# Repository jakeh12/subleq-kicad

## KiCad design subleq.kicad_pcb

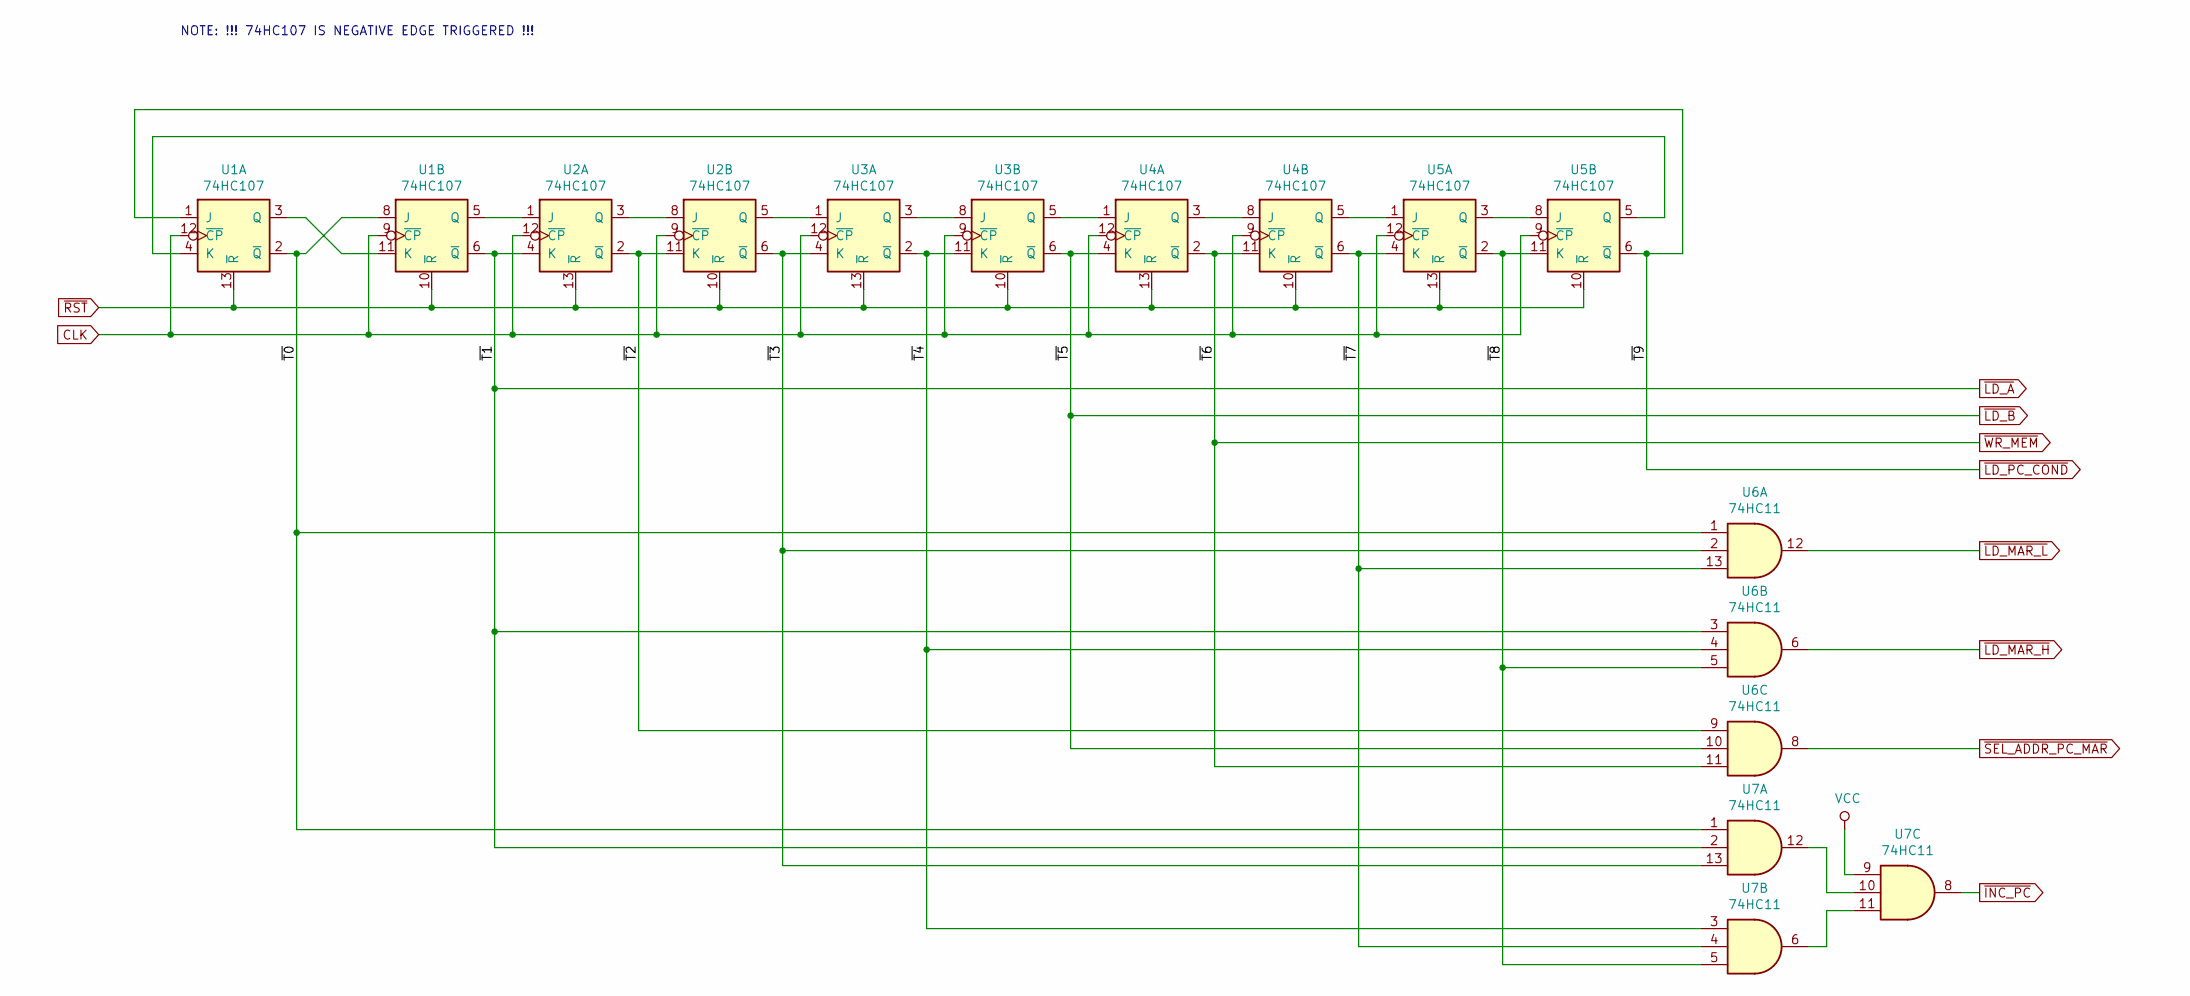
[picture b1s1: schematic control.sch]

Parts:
U1, U2, U3, U4, U5: 74HC107; DIP-14_W7.62mm
U6, U7: 74HC11; DIP-14_W7.62mm

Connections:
/CONTROL/~T0: U1.2 (~Q), U1.8 (J), U6.1, U7.1
/CONTROL/~T2: U2.2 (~Q), U2.11 (K), U6.9
/CONTROL/~T3: U2.6 (~Q), U3.4 (K), U6.2, U7.13
/CONTROL/~T4: U3.2 (~Q), U3.11 (K), U6.4, U7.3
/CONTROL/~T7: U4.6 (~Q), U5.4 (K), U6.13, U7.4
/CONTROL/~T8: U5.2 (~Q), U5.11 (K), U6.5, U7.5
CLK: U1.9 (~CP), U1.12 (~CP), U2.9 (~CP), U2.12 (~CP), U3.9 (~CP), U3.12 (~CP), U4.9 (~CP), U4.12 (~CP), U5.9 (~CP), U5.12 (~CP); also elsewhere on the board
unnamed: U1.4 (K), U5.5 (Q)
unnamed: U1.5 (Q), U2.1 (J)
unnamed: U1.3 (Q), U1.11 (K)
unnamed: U2.3 (Q), U2.8 (J)
unnamed: U2.5 (Q), U3.1 (J)
unnamed: U3.3 (Q), U3.8 (J)
unnamed: U3.5 (Q), U4.1 (J)
unnamed: U4.3 (Q), U4.8 (J)
unnamed: U4.5 (Q), U5.1 (J)
unnamed: U5.3 (Q), U5.8 (J)
unnamed: U7.10, U7.12
unnamed: U7.6, U7.11
VCC: U7.9; also elsewhere on the board
~ADDR_OE: U1.10 (~R), U1.13 (~R), U2.10 (~R), U2.13 (~R), U3.10 (~R), U3.13 (~R), U4.10 (~R), U4.13 (~R), U5.10 (~R), U5.13 (~R); also elsewhere on the board
~INC_PC: U7.8; also elsewhere on the board
~LD_A: U1.6 (~Q), U2.4 (K), U6.3, U7.2; also elsewhere on the board
~LD_B: U3.6 (~Q), U4.4 (K), U6.10; also elsewhere on the board
~LD_MAR_H: U6.6; also elsewhere on the board
~LD_MAR_L: U6.12; also elsewhere on the board
~LD_PC_COND: U1.1 (J), U5.6 (~Q); also elsewhere on the board
~SEL_ADDR_PC_MAR: U6.8; also elsewhere on the board
~WR_MEM: U4.2 (~Q), U4.11 (K), U6.11; also elsewhere on the board

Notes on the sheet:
NOTE: !!! 74HC107 IS NEGATIVE EDGE TRIGGERED !!!

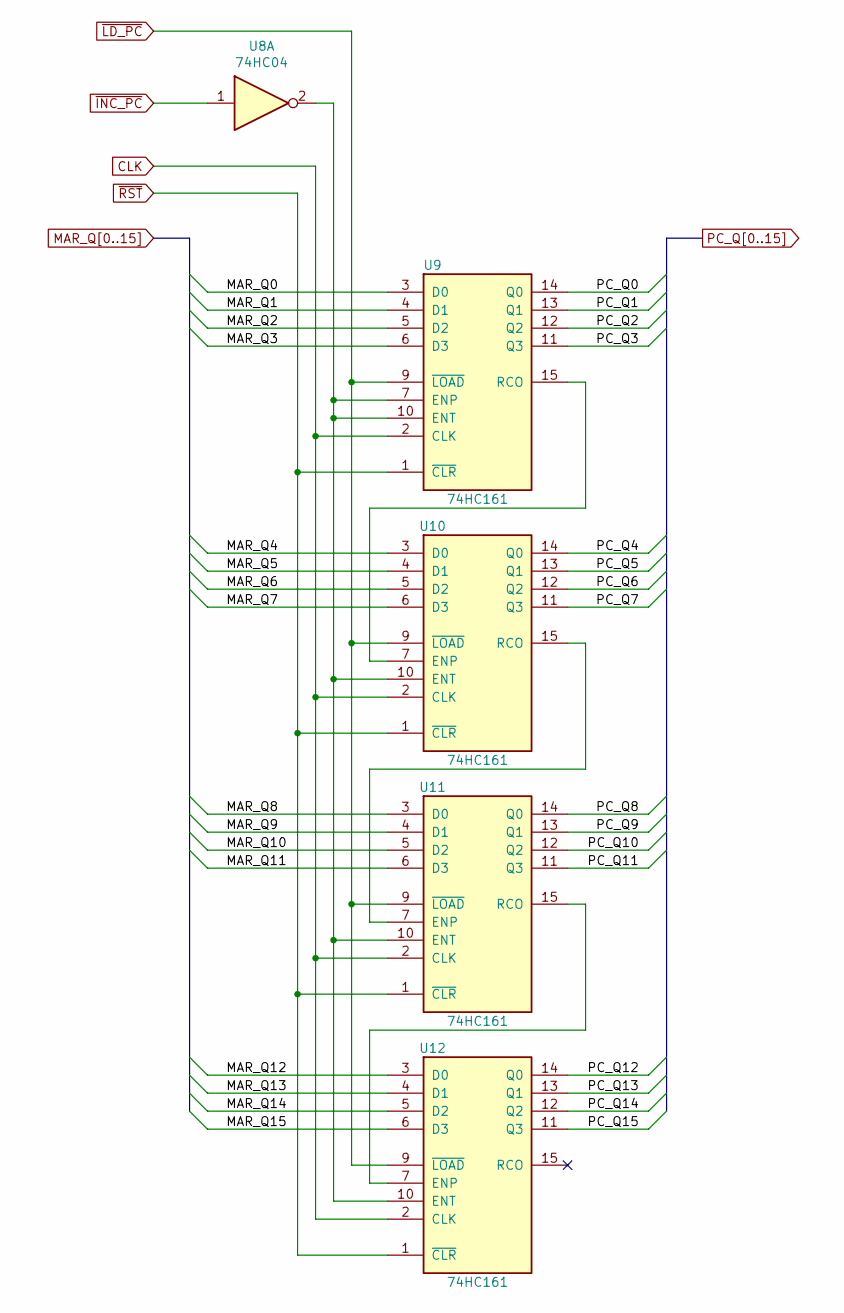
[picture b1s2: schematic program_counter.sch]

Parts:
U8: 74HC04; DIP-14_W7.62mm
U9, U10, U11, U12: 74HC161; DIP-16_W7.62mm

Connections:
CLK: U9.2 (CLK), U10.2 (CLK), U11.2 (CLK), U12.2 (CLK); also elsewhere on the board
MAR_Q0: U9.3 (D0); also elsewhere on the board
MAR_Q1: U9.4 (D1); also elsewhere on the board
MAR_Q2: U9.5 (D2); also elsewhere on the board
MAR_Q3: U9.6 (D3); also elsewhere on the board
MAR_Q4: U10.3 (D0); also elsewhere on the board
MAR_Q5: U10.4 (D1); also elsewhere on the board
MAR_Q6: U10.5 (D2); also elsewhere on the board
MAR_Q7: U10.6 (D3); also elsewhere on the board
MAR_Q8: U11.3 (D0); also elsewhere on the board
MAR_Q9: U11.4 (D1); also elsewhere on the board
MAR_Q10: U11.5 (D2); also elsewhere on the board
MAR_Q11: U11.6 (D3); also elsewhere on the board
MAR_Q12: U12.3 (D0); also elsewhere on the board
MAR_Q13: U12.4 (D1); also elsewhere on the board
MAR_Q14: U12.5 (D2); also elsewhere on the board
MAR_Q15: U12.6 (D3); also elsewhere on the board
unnamed: U9.15 (RCO), U10.7 (ENP)
unnamed: U8.2, U9.7 (ENP), U9.10 (ENT), U10.10 (ENT), U11.10 (ENT), U12.10 (ENT)
unnamed: U10.15 (RCO), U11.7 (ENP)
unnamed: U11.15 (RCO), U12.7 (ENP)
PC_Q0: U9.14 (Q0); also elsewhere on the board
PC_Q1: U9.13 (Q1); also elsewhere on the board
PC_Q2: U9.12 (Q2); also elsewhere on the board
PC_Q3: U9.11 (Q3); also elsewhere on the board
PC_Q4: U10.14 (Q0); also elsewhere on the board
PC_Q5: U10.13 (Q1); also elsewhere on the board
PC_Q6: U10.12 (Q2); also elsewhere on the board
PC_Q7: U10.11 (Q3); also elsewhere on the board
PC_Q8: U11.14 (Q0); also elsewhere on the board
PC_Q9: U11.13 (Q1); also elsewhere on the board
PC_Q10: U11.12 (Q2); also elsewhere on the board
PC_Q11: U11.11 (Q3); also elsewhere on the board
PC_Q12: U12.14 (Q0); also elsewhere on the board
PC_Q13: U12.13 (Q1); also elsewhere on the board
PC_Q14: U12.12 (Q2); also elsewhere on the board
PC_Q15: U12.11 (Q3); also elsewhere on the board
VCC: U9.16 (VCC), U10.16 (VCC), U11.16 (VCC), U12.16 (VCC); also elsewhere on the board
~ADDR_OE: U9.1 (~CLR), U9.8 (GND), U10.1 (~CLR), U10.8 (GND), U11.1 (~CLR), U11.8 (GND), U12.1 (~CLR), U12.8 (GND); also elsewhere on the board
~INC_PC: U8.1; also elsewhere on the board
~LD_PC: U9.9 (~LOAD), U10.9 (~LOAD), U11.9 (~LOAD), U12.9 (~LOAD); also elsewhere on the board

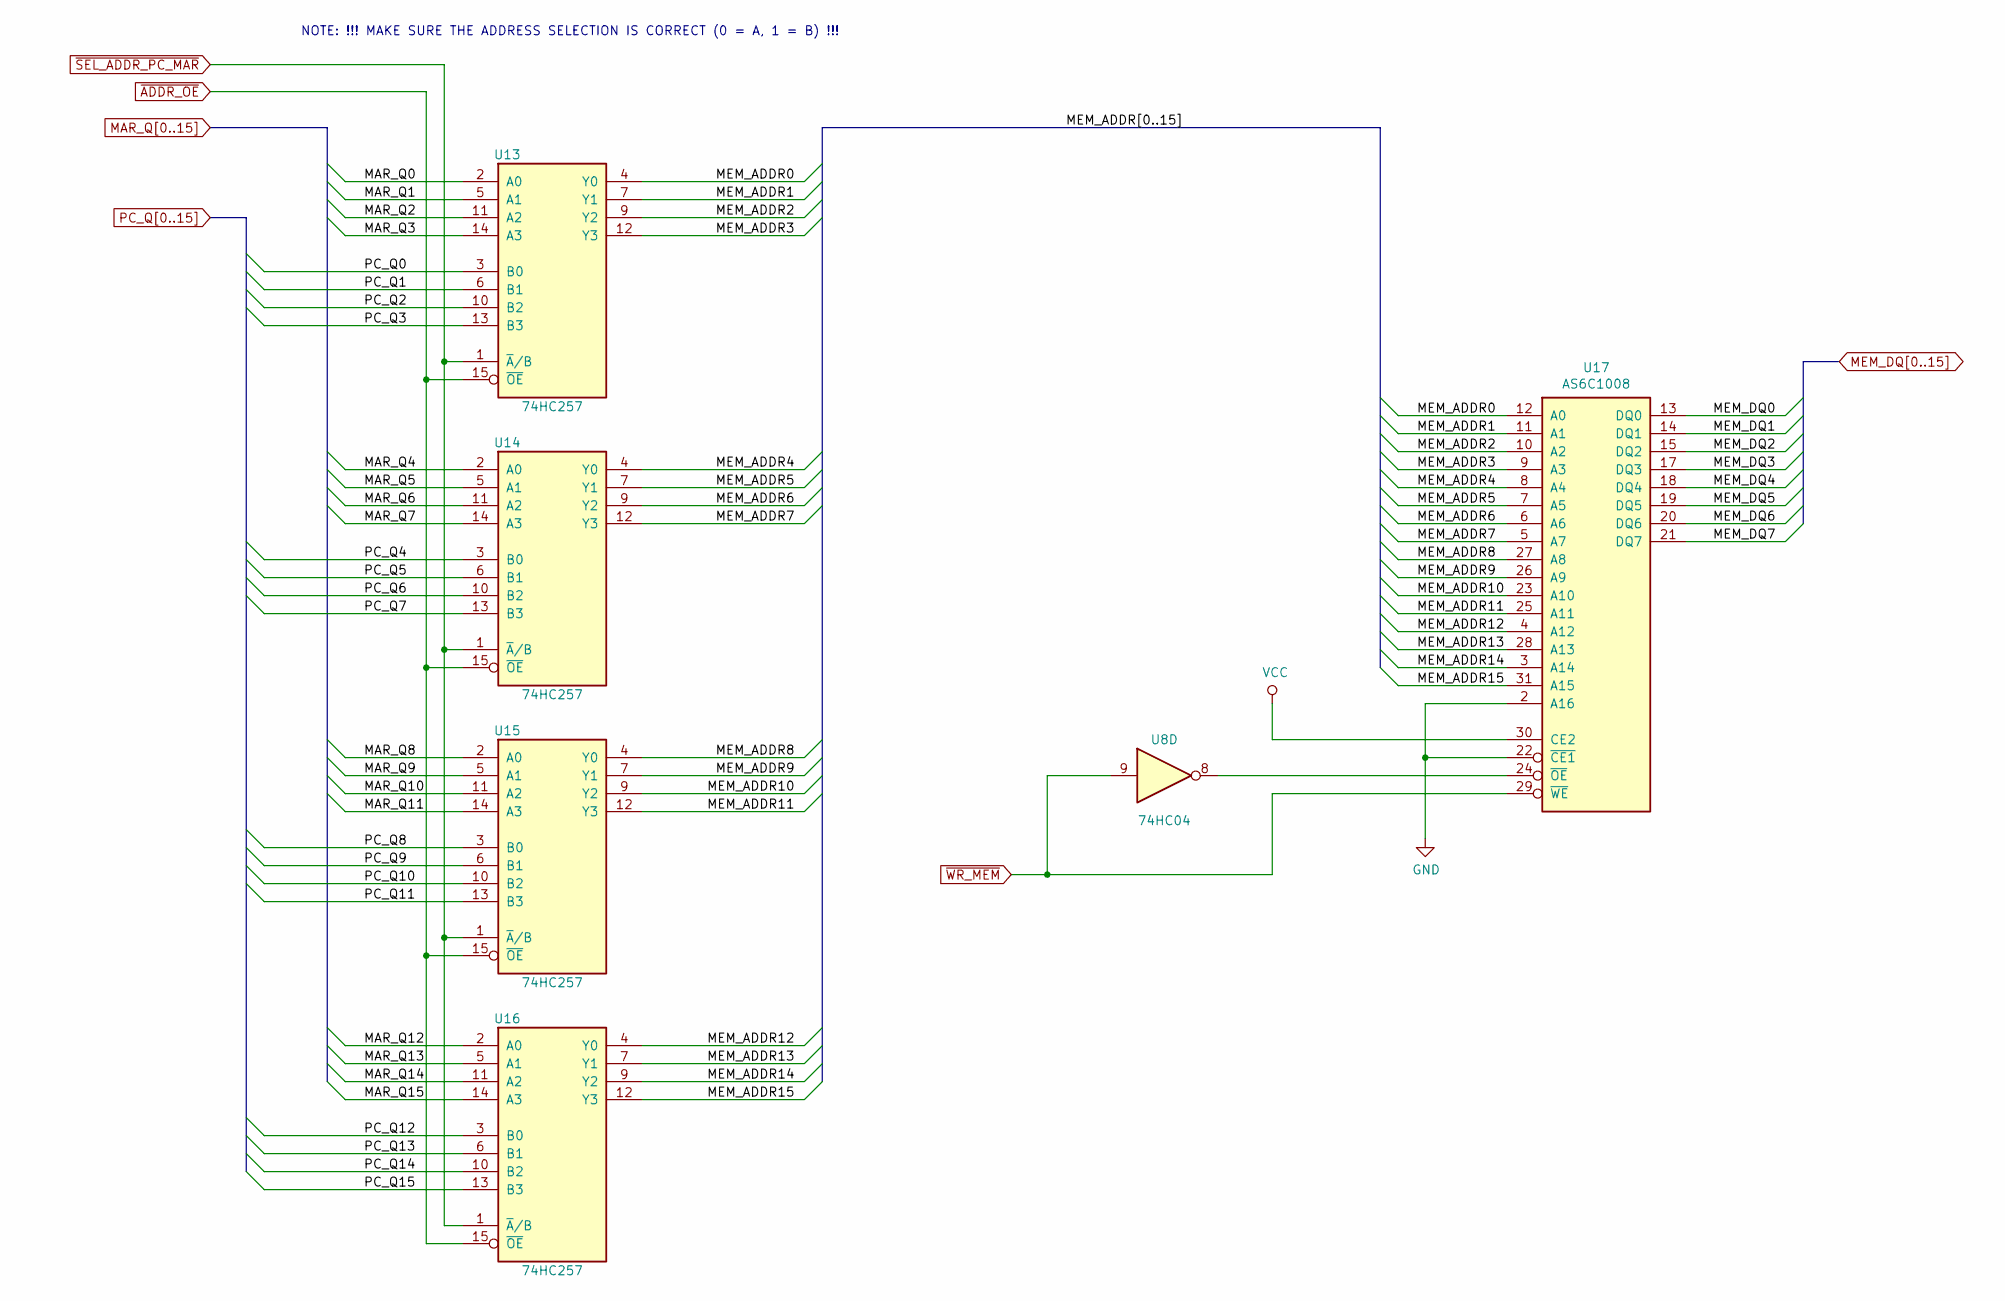
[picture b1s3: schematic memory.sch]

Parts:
U8: 74HC04; DIP-14_W7.62mm
U13, U14, U15, U16: 74HC257; DIP-16_W7.62mm
U17: AS6C1008; DIP-32_W15.24mm

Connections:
/MEMORY/MEM_ADDR0: U13.4 (Y0), U17.12 (A0)
/MEMORY/MEM_ADDR1: U13.7 (Y1), U17.11 (A1)
/MEMORY/MEM_ADDR2: U13.9 (Y2), U17.10 (A2)
/MEMORY/MEM_ADDR3: U13.12 (Y3), U17.9 (A3)
/MEMORY/MEM_ADDR4: U14.4 (Y0), U17.8 (A4)
/MEMORY/MEM_ADDR5: U14.7 (Y1), U17.7 (A5)
/MEMORY/MEM_ADDR6: U14.9 (Y2), U17.6 (A6)
/MEMORY/MEM_ADDR7: U14.12 (Y3), U17.5 (A7)
/MEMORY/MEM_ADDR8: U15.4 (Y0), U17.27 (A8)
/MEMORY/MEM_ADDR9: U15.7 (Y1), U17.26 (A9)
/MEMORY/MEM_ADDR10: U15.9 (Y2), U17.23 (A10)
/MEMORY/MEM_ADDR11: U15.12 (Y3), U17.25 (A11)
/MEMORY/MEM_ADDR12: U16.4 (Y0), U17.4 (A12)
/MEMORY/MEM_ADDR13: U16.7 (Y1), U17.28 (A13)
/MEMORY/MEM_ADDR14: U16.9 (Y2), U17.3 (A14)
/MEMORY/MEM_ADDR15: U16.12 (Y3), U17.31 (A15)
MAR_Q0: U13.2 (A0); also elsewhere on the board
MAR_Q1: U13.5 (A1); also elsewhere on the board
MAR_Q2: U13.11 (A2); also elsewhere on the board
MAR_Q3: U13.14 (A3); also elsewhere on the board
MAR_Q4: U14.2 (A0); also elsewhere on the board
MAR_Q5: U14.5 (A1); also elsewhere on the board
MAR_Q6: U14.11 (A2); also elsewhere on the board
MAR_Q7: U14.14 (A3); also elsewhere on the board
MAR_Q8: U15.2 (A0); also elsewhere on the board
MAR_Q9: U15.5 (A1); also elsewhere on the board
MAR_Q10: U15.11 (A2); also elsewhere on the board
MAR_Q11: U15.14 (A3); also elsewhere on the board
MAR_Q12: U16.2 (A0); also elsewhere on the board
MAR_Q13: U16.5 (A1); also elsewhere on the board
MAR_Q14: U16.11 (A2); also elsewhere on the board
MAR_Q15: U16.14 (A3); also elsewhere on the board
MEM_DQ0: U17.13 (DQ0); also elsewhere on the board
MEM_DQ1: U17.14 (DQ1); also elsewhere on the board
MEM_DQ2: U17.15 (DQ2); also elsewhere on the board
MEM_DQ3: U17.17 (DQ3); also elsewhere on the board
MEM_DQ4: U17.18 (DQ4); also elsewhere on the board
MEM_DQ5: U17.19 (DQ5); also elsewhere on the board
MEM_DQ6: U17.20 (DQ6); also elsewhere on the board
MEM_DQ7: U17.21 (DQ7); also elsewhere on the board
unnamed: U8.8, U17.24 (~OE)
PC_Q0: U13.3 (B0); also elsewhere on the board
PC_Q1: U13.6 (B1); also elsewhere on the board
PC_Q2: U13.10 (B2); also elsewhere on the board
PC_Q3: U13.13 (B3); also elsewhere on the board
PC_Q4: U14.3 (B0); also elsewhere on the board
PC_Q5: U14.6 (B1); also elsewhere on the board
PC_Q6: U14.10 (B2); also elsewhere on the board
PC_Q7: U14.13 (B3); also elsewhere on the board
PC_Q8: U15.3 (B0); also elsewhere on the board
PC_Q9: U15.6 (B1); also elsewhere on the board
PC_Q10: U15.10 (B2); also elsewhere on the board
PC_Q11: U15.13 (B3); also elsewhere on the board
PC_Q12: U16.3 (B0); also elsewhere on the board
PC_Q13: U16.6 (B1); also elsewhere on the board
PC_Q14: U16.10 (B2); also elsewhere on the board
PC_Q15: U16.13 (B3); also elsewhere on the board
VCC: U13.16 (VCC), U14.16 (VCC), U15.16 (VCC), U16.16 (VCC), U17.30 (CE2), U17.32 (VCC); also elsewhere on the board
~ADDR_OE: U13.8 (GND), U13.15 (~OE), U14.8 (GND), U14.15 (~OE), U15.8 (GND), U15.15 (~OE), U16.8 (GND), U16.15 (~OE), U17.2 (A16), U17.16 (GND), U17.22 (~CE1); also elsewhere on the board
~SEL_ADDR_PC_MAR: U13.1 (~A~/B), U14.1 (~A~/B), U15.1 (~A~/B), U16.1 (~A~/B); also elsewhere on the board
~WR_MEM: U8.9, U17.29 (~WE); also elsewhere on the board

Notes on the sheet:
NOTE: !!! MAKE SURE THE ADDRESS SELECTION IS CORRECT (0 = A, 1 = B) !!!

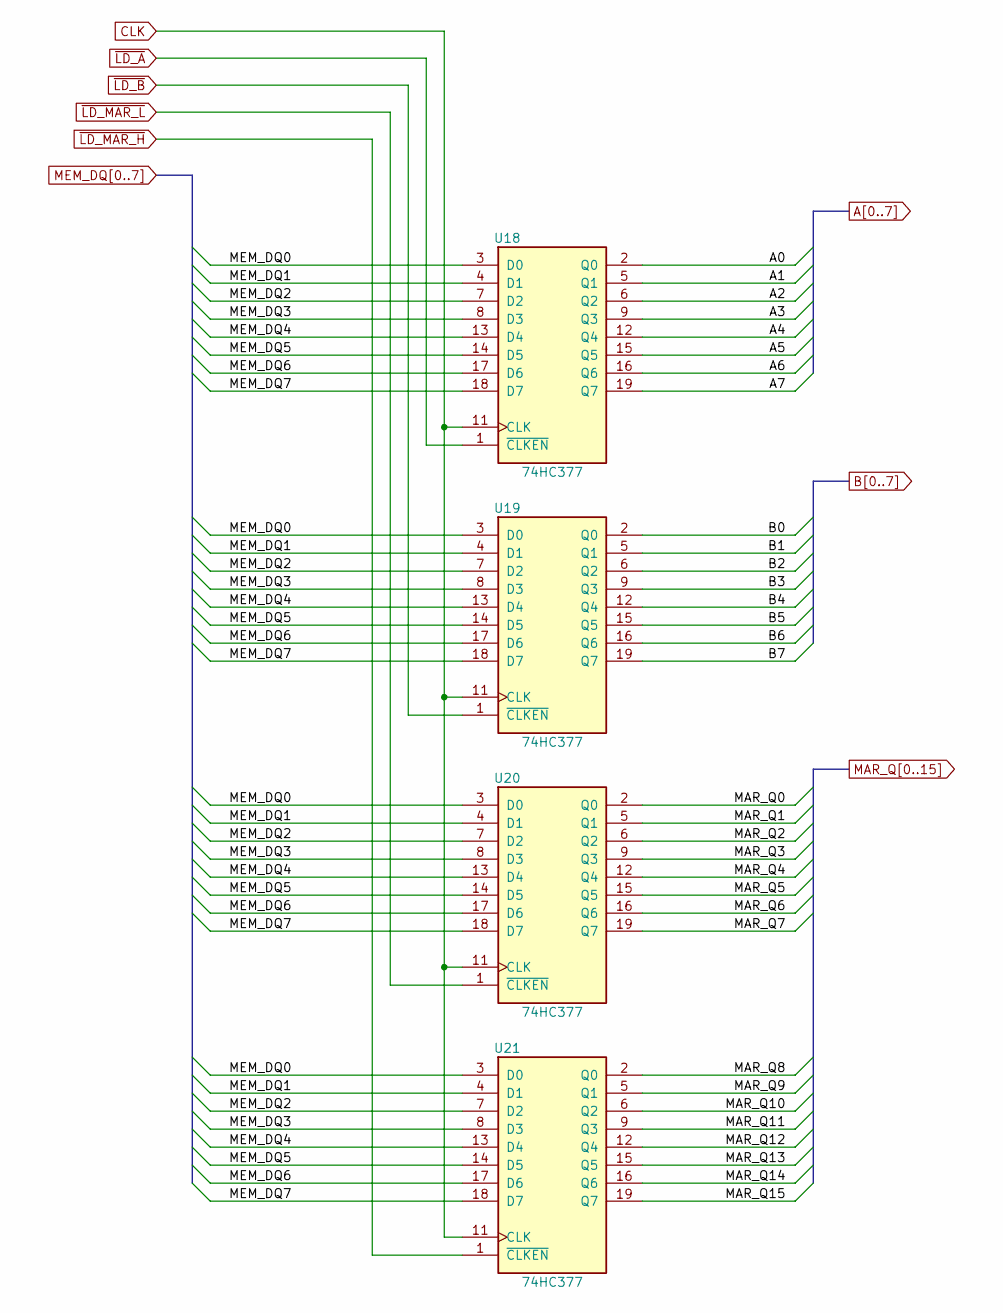
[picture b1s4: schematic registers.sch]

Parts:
U18, U19, U20, U21: 74HC377; DIP-20_W7.62mm

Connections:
A0: U18.2 (Q0); also elsewhere on the board
A1: U18.5 (Q1); also elsewhere on the board
A2: U18.6 (Q2); also elsewhere on the board
A3: U18.9 (Q3); also elsewhere on the board
A4: U18.12 (Q4); also elsewhere on the board
A5: U18.15 (Q5); also elsewhere on the board
A6: U18.16 (Q6); also elsewhere on the board
A7: U18.19 (Q7); also elsewhere on the board
B0: U19.2 (Q0); also elsewhere on the board
B1: U19.5 (Q1); also elsewhere on the board
B2: U19.6 (Q2); also elsewhere on the board
B3: U19.9 (Q3); also elsewhere on the board
B4: U19.12 (Q4); also elsewhere on the board
B5: U19.15 (Q5); also elsewhere on the board
B6: U19.16 (Q6); also elsewhere on the board
B7: U19.19 (Q7); also elsewhere on the board
CLK: U18.11 (CLK), U19.11 (CLK), U20.11 (CLK), U21.11 (CLK); also elsewhere on the board
MAR_Q0: U20.2 (Q0); also elsewhere on the board
MAR_Q1: U20.5 (Q1); also elsewhere on the board
MAR_Q2: U20.6 (Q2); also elsewhere on the board
MAR_Q3: U20.9 (Q3); also elsewhere on the board
MAR_Q4: U20.12 (Q4); also elsewhere on the board
MAR_Q5: U20.15 (Q5); also elsewhere on the board
MAR_Q6: U20.16 (Q6); also elsewhere on the board
MAR_Q7: U20.19 (Q7); also elsewhere on the board
MAR_Q8: U21.2 (Q0); also elsewhere on the board
MAR_Q9: U21.5 (Q1); also elsewhere on the board
MAR_Q10: U21.6 (Q2); also elsewhere on the board
MAR_Q11: U21.9 (Q3); also elsewhere on the board
MAR_Q12: U21.12 (Q4); also elsewhere on the board
MAR_Q13: U21.15 (Q5); also elsewhere on the board
MAR_Q14: U21.16 (Q6); also elsewhere on the board
MAR_Q15: U21.19 (Q7); also elsewhere on the board
MEM_DQ0: U18.3 (D0), U19.3 (D0), U20.3 (D0), U21.3 (D0); also elsewhere on the board
MEM_DQ1: U18.4 (D1), U19.4 (D1), U20.4 (D1), U21.4 (D1); also elsewhere on the board
MEM_DQ2: U18.7 (D2), U19.7 (D2), U20.7 (D2), U21.7 (D2); also elsewhere on the board
MEM_DQ3: U18.8 (D3), U19.8 (D3), U20.8 (D3), U21.8 (D3); also elsewhere on the board
MEM_DQ4: U18.13 (D4), U19.13 (D4), U20.13 (D4), U21.13 (D4); also elsewhere on the board
MEM_DQ5: U18.14 (D5), U19.14 (D5), U20.14 (D5), U21.14 (D5); also elsewhere on the board
MEM_DQ6: U18.17 (D6), U19.17 (D6), U20.17 (D6), U21.17 (D6); also elsewhere on the board
MEM_DQ7: U18.18 (D7), U19.18 (D7), U20.18 (D7), U21.18 (D7); also elsewhere on the board
VCC: U18.20 (VCC), U19.20 (VCC), U20.20 (VCC), U21.20 (VCC); also elsewhere on the board
~ADDR_OE: U18.10 (GND), U19.10 (GND), U20.10 (GND), U21.10 (GND); also elsewhere on the board
~LD_A: U18.1 (~CLKEN); also elsewhere on the board
~LD_B: U19.1 (~CLKEN); also elsewhere on the board
~LD_MAR_H: U21.1 (~CLKEN); also elsewhere on the board
~LD_MAR_L: U20.1 (~CLKEN); also elsewhere on the board

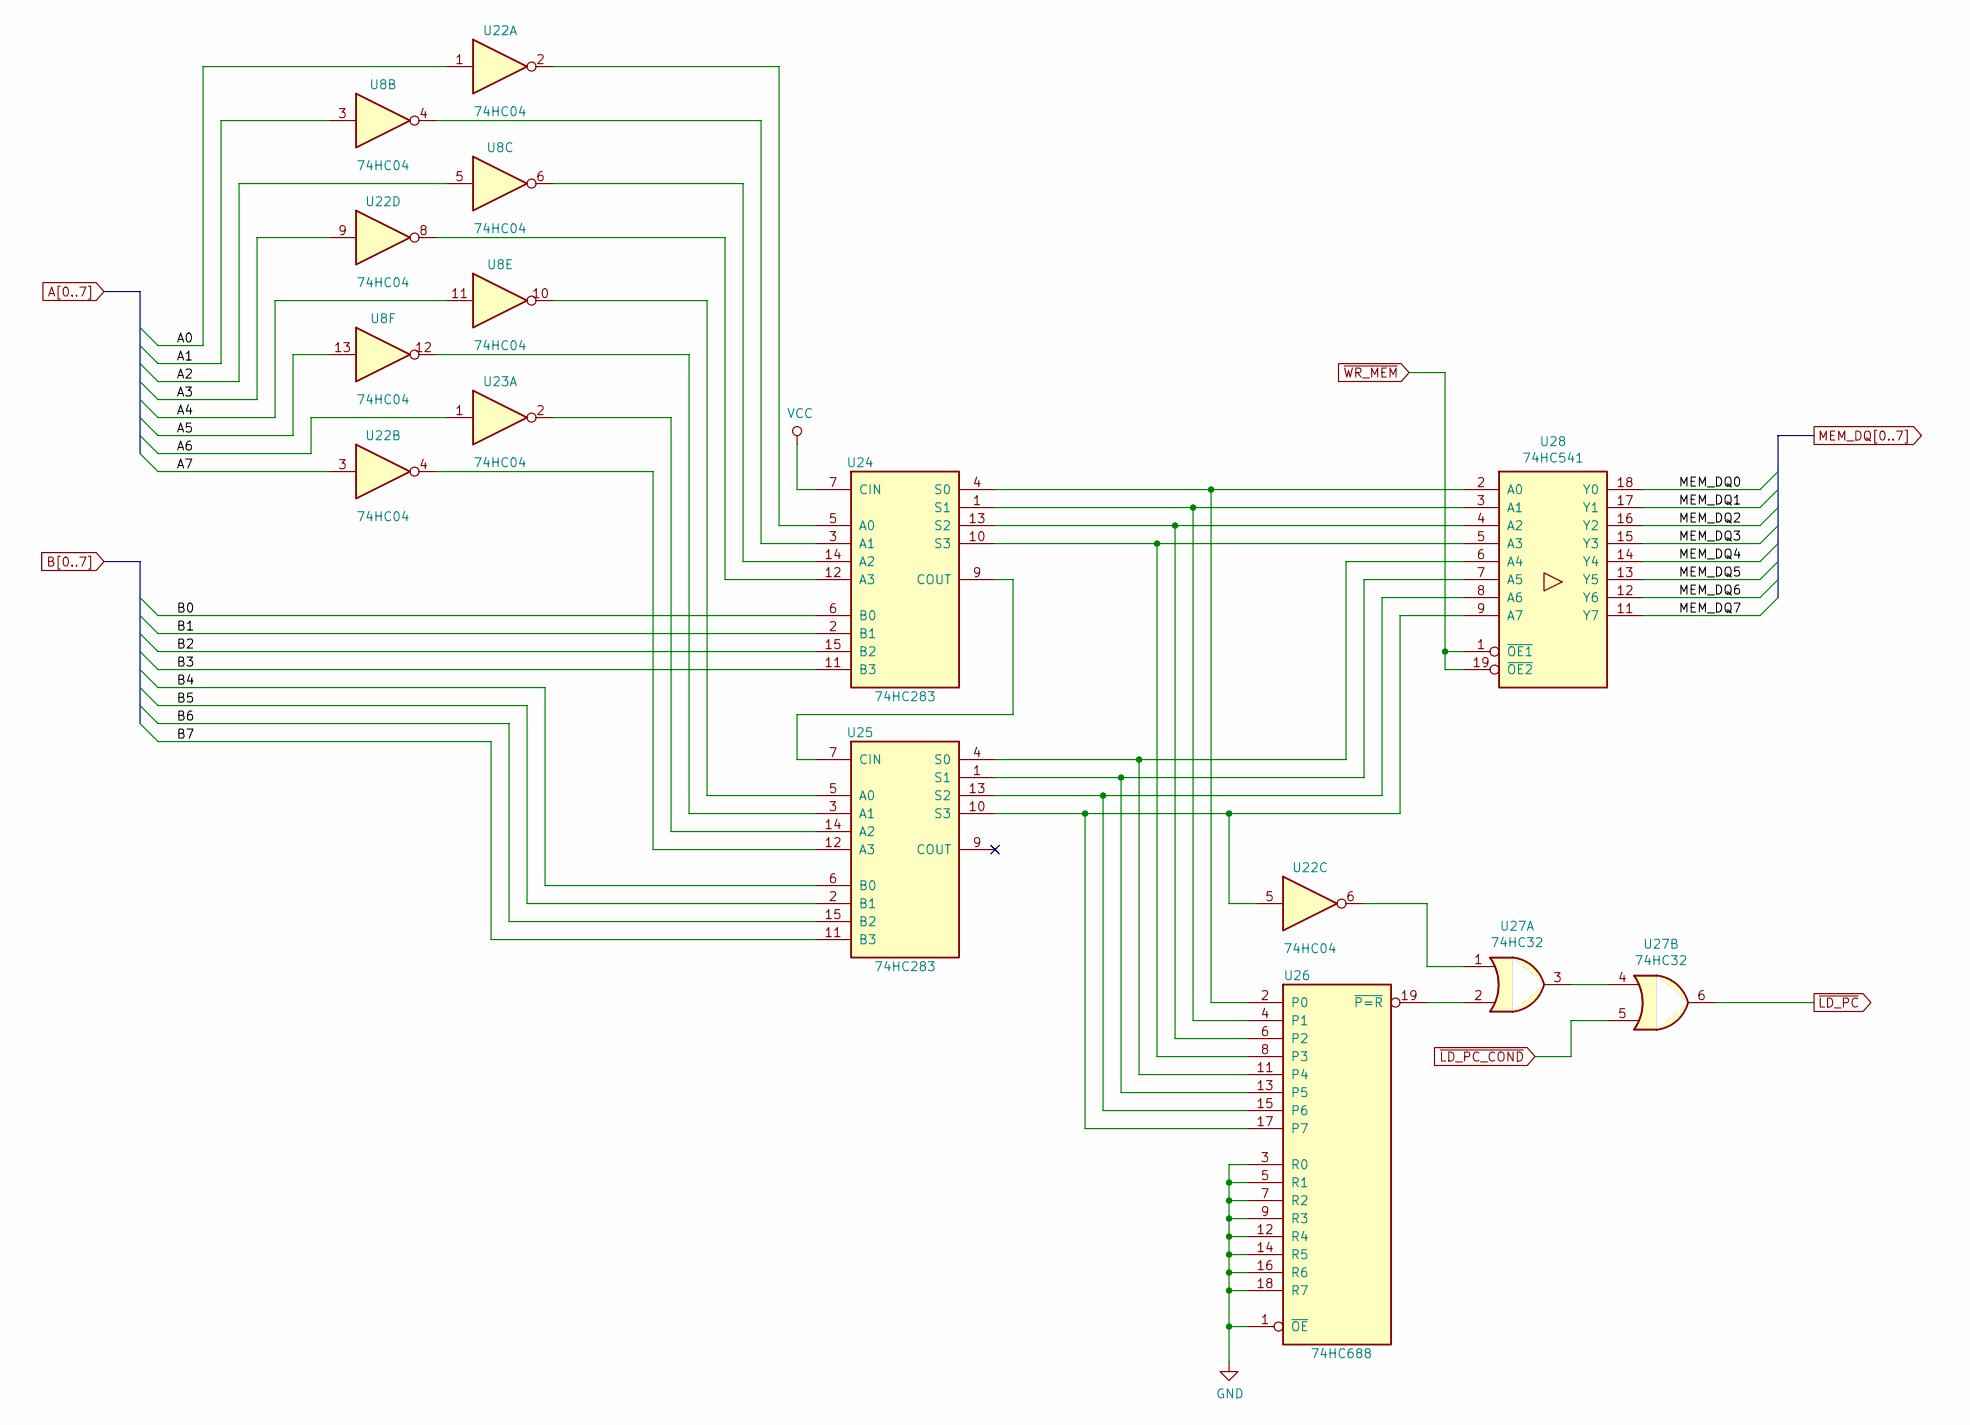
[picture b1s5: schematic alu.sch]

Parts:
U8, U22, U23: 74HC04; DIP-14_W7.62mm
U24, U25: 74HC283; DIP-16_W7.62mm
U26: 74HC688; DIP-20_W7.62mm
U27: 74HC32; DIP-14_W7.62mm
U28: 74HC541; DIP-20_W7.62mm

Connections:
A0: U22.1; also elsewhere on the board
A1: U8.3; also elsewhere on the board
A2: U8.5; also elsewhere on the board
A3: U22.9; also elsewhere on the board
A4: U8.11; also elsewhere on the board
A5: U8.13; also elsewhere on the board
A6: U23.1; also elsewhere on the board
A7: U22.3; also elsewhere on the board
B0: U24.6 (B0); also elsewhere on the board
B1: U24.2 (B1); also elsewhere on the board
B2: U24.15 (B2); also elsewhere on the board
B3: U24.11 (B3); also elsewhere on the board
B4: U25.6 (B0); also elsewhere on the board
B5: U25.2 (B1); also elsewhere on the board
B6: U25.15 (B2); also elsewhere on the board
B7: U25.11 (B3); also elsewhere on the board
MEM_DQ0: U28.18 (Y0); also elsewhere on the board
MEM_DQ1: U28.17 (Y1); also elsewhere on the board
MEM_DQ2: U28.16 (Y2); also elsewhere on the board
MEM_DQ3: U28.15 (Y3); also elsewhere on the board
MEM_DQ4: U28.14 (Y4); also elsewhere on the board
MEM_DQ5: U28.13 (Y5); also elsewhere on the board
MEM_DQ6: U28.12 (Y6); also elsewhere on the board
MEM_DQ7: U28.11 (Y7); also elsewhere on the board
unnamed: U22.2, U24.5 (A0)
unnamed: U22.4, U25.12 (A3)
unnamed: U22.5, U25.10 (S3), U26.17 (P7), U28.9 (A7)
unnamed: U22.6, U27.1
unnamed: U22.8, U24.12 (A3)
unnamed: U23.2, U25.14 (A2)
unnamed: U24.1 (S1), U26.4 (P1), U28.3 (A1)
unnamed: U8.4, U24.3 (A1)
unnamed: U24.4 (S0), U26.2 (P0), U28.2 (A0)
unnamed: U24.9 (COUT), U25.7 (CIN)
unnamed: U24.10 (S3), U26.8 (P3), U28.5 (A3)
unnamed: U24.13 (S2), U26.6 (P2), U28.4 (A2)
unnamed: U8.6, U24.14 (A2)
unnamed: U25.1 (S1), U26.13 (P5), U28.7 (A5)
unnamed: U8.12, U25.3 (A1)
unnamed: U25.4 (S0), U26.11 (P4), U28.6 (A4)
unnamed: U8.10, U25.5 (A0)
unnamed: U25.13 (S2), U26.15 (P6), U28.8 (A6)
unnamed: U26.19 (~P=R), U27.2
unnamed: U27.3, U27.4
VCC: U24.7 (CIN), U24.16 (VCC), U25.16 (VCC), U26.20 (VCC), U28.20 (VCC); also elsewhere on the board
~ADDR_OE: U24.8 (GND), U25.8 (GND), U26.1 (~OE), U26.3 (R0), U26.5 (R1), U26.7 (R2), U26.9 (R3), U26.10 (GND), U26.12 (R4), U26.14 (R5), U26.16 (R6), U26.18 (R7), U28.10 (GND); also elsewhere on the board
~LD_PC: U27.6; also elsewhere on the board
~LD_PC_COND: U27.5; also elsewhere on the board
~WR_MEM: U28.1 (~OE1), U28.19 (~OE2); also elsewhere on the board

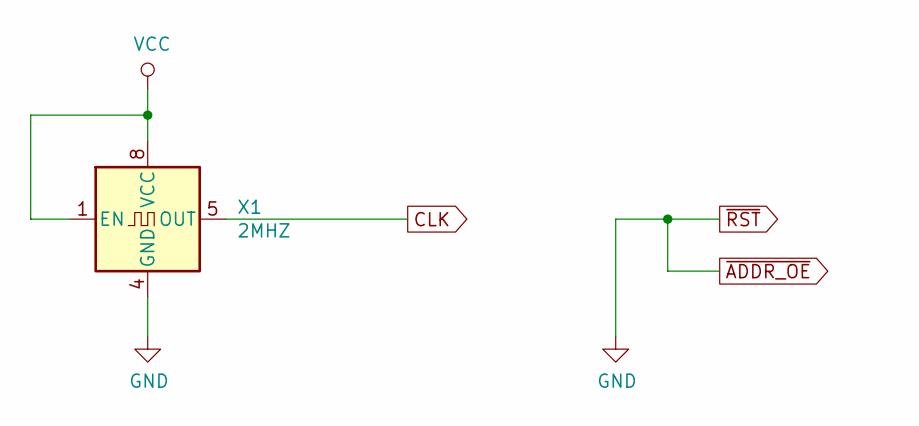
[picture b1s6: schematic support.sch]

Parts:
X1: 2MHZ; Oscillator_DIP-8

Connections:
CLK: X1.5 (OUT); also elsewhere on the board
VCC: X1.1 (EN), X1.8 (VCC); also elsewhere on the board
~ADDR_OE: X1.4 (GND); also elsewhere on the board

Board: 2 copper layers, 29 parts (0 on the bottom side), 127 nets, no tracks yet.

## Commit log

2019-01-26 started pcb file
2019-01-27 commit after a crash, recovered backups
2019-01-27 finished ALU and registers
2019-01-27 backup before registers alu split
2019-01-27 split alu complete
2019-01-27 split alu regs complete
2019-01-27 created mux part
2019-01-27 mem muxing done
2019-01-27 added labels
2019-01-27 done for the night passing drc
2019-01-27 calling it a night
